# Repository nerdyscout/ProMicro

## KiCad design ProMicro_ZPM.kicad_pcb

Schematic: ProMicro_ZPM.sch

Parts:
A1: Sparkfun_Pro_Micro_3V3; Sparkfun_Pro_Micro
C1: 10µF; CP_Elec_4x3
C2: 1µ; C_0603_1608Metric
C3, C4: 4.7µ; C_0603_1608Metric
J1: Screw_Terminal_01x05; TerminalBlock_TE_282834-5_1x05_P2.54mm_Horizontal
J3: JST; JST_PH_S2B-PH-SM4-TB_1x02-1MP_P2.00mm_Horizontal
JP2, JP3: SolderJumper_3_Bridged12; SolderJumper-3_P1.3mm_Bridged12_RoundedPad1.0x1.5mm
JP4: SolderJumper_2_Open; SolderJumper-2_P1.3mm_Open_RoundedPad1.0x1.5mm
L1: CDRH2D18_HPNP-100C; HPNP-100NC
LOGO1: Logo_Open_Hardware_Small; OSHW-Symbol_6.7x6mm_SilkScreen
Q1: BC847; SOT-23
R1: 2k; R_0603_1608Metric
TP1: TestPoint; TestPoint_Pad_D2.5mm
U1: LTC3588EDD-1PBF; MSOP-10-1EP_3x3mm_P0.5mm_EP1.68x1.88mm_ThermalVias
U2: MCP73831-2-OT; SOT-23-5

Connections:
+3V3: A1.21, C1.1, J1.3, L1.1, U1.6
/D0: JP2.2 (C), U1.9
/D1: JP3.2 (C), U1.8
/Vin2: C4.1, JP2.3 (B), JP3.1 (A), U1.7
GND: A1.4, A1.23, C1.2, C3.2, C4.2, J1.1, J3.1, JP2.1 (A), JP3.3 (B), Q1.2, R1.2, U1.11, U2.2
unnamed: C2.1, U1.3
unnamed: J1.4, U1.2
unnamed: J1.5, U1.1
unnamed: JP4.2 (B), Q1.1, U1.10
unnamed: L1.2, U1.5
unnamed: R1.1, U2.5
Reset: A1.22, JP4.1 (A), Q1.3
VBAT: C2.2, C3.1, J1.2, J3.2, TP1.1, U1.4, U2.3
VCC: A1.24, U2.4

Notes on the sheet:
default Vout = 3.3V

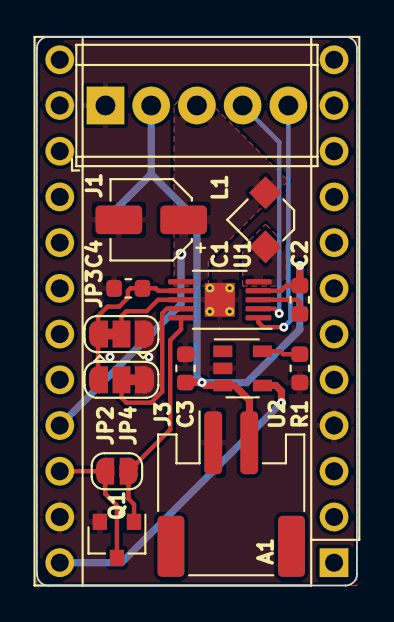
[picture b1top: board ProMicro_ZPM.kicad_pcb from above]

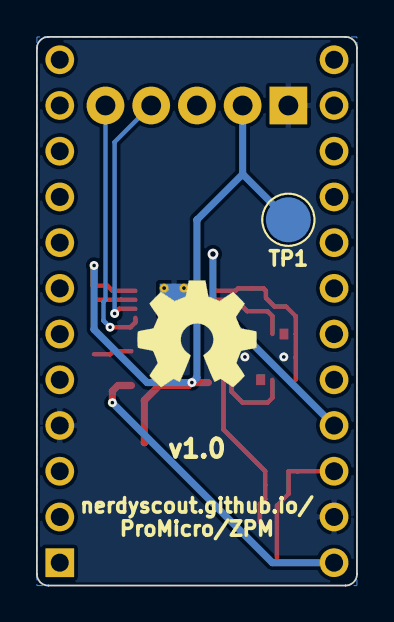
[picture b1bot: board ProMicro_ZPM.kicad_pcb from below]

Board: 2 copper layers, 17.8 x 30.5 mm, 17 parts (2 on the bottom side), 14 nets.

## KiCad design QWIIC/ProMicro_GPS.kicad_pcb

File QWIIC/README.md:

# ProMicro_QWIIC
This module can be mounted to an [Arduino Pro Mini](https://www.sparkfun.com/products/11113), [Arduino Nano](https://store.arduino.cc/arduino-nano), [Sparkfun Pro Micro](https://www.sparkfun.com/products/12587), or any other pincompatible MCU running with 3.3V.

## Documentation 
All files can be found on [Github](https://github.com/nerdyscout/ProMicro/tree/master/QWIIC).

### Schematic

### BoM
  * [interactiveHTMLBoM](https://nerdyscout.github.io/ProMicro/QWIIC/docs/bom/QWIIC-ibom.html)
  * [octopart](docs/bom/QWIIC-bom_octopart.csv)

## Hardware 
### Layout

### Gerbers
can be found within the Github [repository](gerbers).

## external
### Links
  * [hackaday.io](https://hackaday.io/project/171898-promicro)

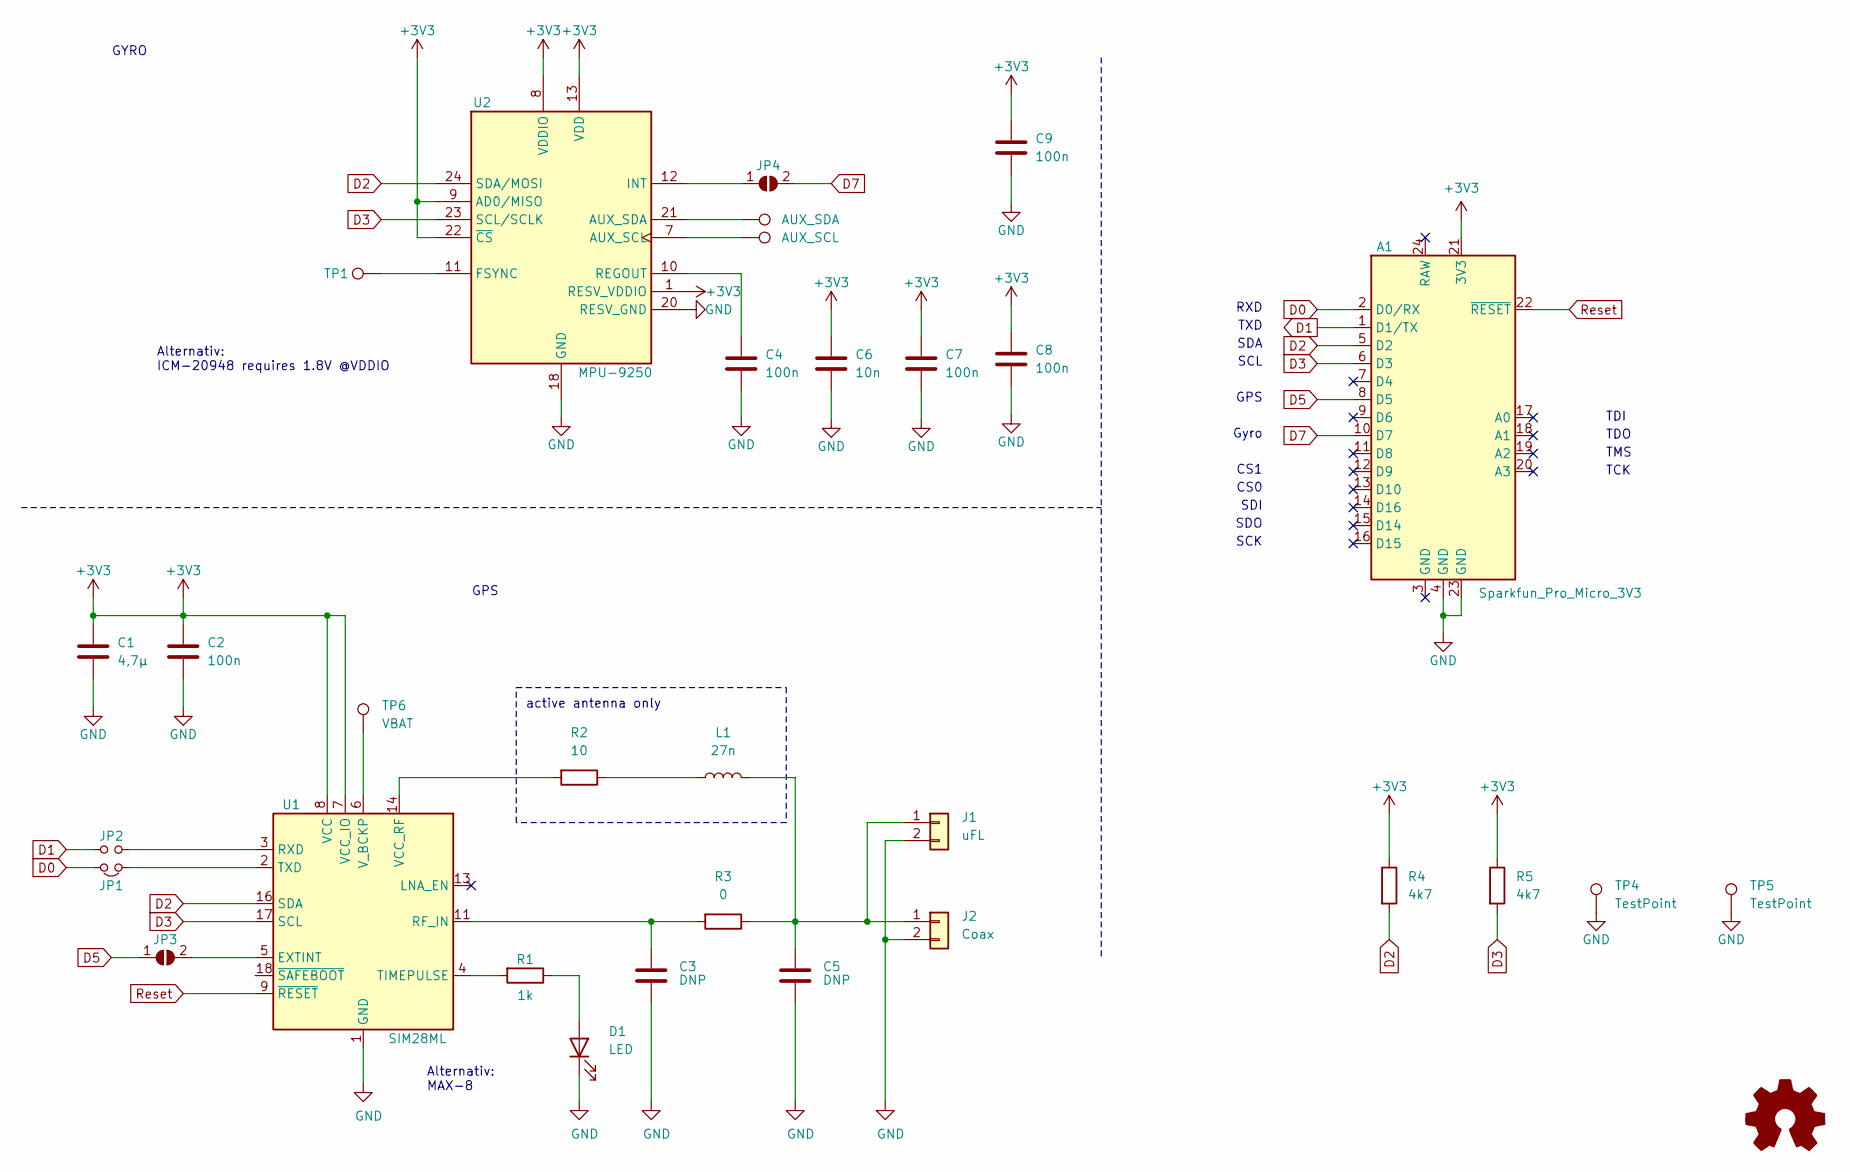
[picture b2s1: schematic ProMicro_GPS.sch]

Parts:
A1: Sparkfun_Pro_Micro_3V3; Sparkfun_Pro_Micro
C1: 4,7µ; C_0603_1608Metric; LCSC# C19666
C2, C4, C7, C8: 100n; C_0402_1005Metric; LCSC# C1525
C3, C5: DNP; C_0402_1005Metric
C6: 10n; C_0402_1005Metric; LCSC# C15195
C9: 100n; C_0402_1005Metric; LCSC# C15195
D1: LED; LED_0603_1608Metric; LCSC# C72041
J1: uFL; U.FL_Hirose_U.FL-R-SMT-1_Vertical
J2: Coax; SMA_Samtec_SMA-J-P-H-ST-EM1_EdgeMount
JP1: Jumper_NC_Small; SolderJumper-2_P1.3mm_Bridged_RoundedPad1.0x1.5mm
JP2: Jumper_NO_Small; SolderJumper-2_P1.3mm_Open_RoundedPad1.0x1.5mm
JP3, JP4: SolderJumper_2_Open; SolderJumper-2_P1.3mm_Open_RoundedPad1.0x1.5mm
L1: 27n; L_0402_1005Metric
LOGO1: Logo_Open_Hardware_Small; OSHW-Symbol_6.7x6mm_SilkScreen
R1: 1k; R_0402_1005Metric; LCSC# C11702
R2: 10; R_0402_1005Metric
R3: 0; R_0402_1005Metric; LCSC# C17168
R4, R5: 4k7; R_0402_1005Metric; LCSC# C25900
TP1: FSYNC; TestPoint_Pad_D1.5mm
TP2: AUX_SDA; TestPoint_Pad_D1.5mm
TP3: AUX_SCL; TestPoint_Pad_D1.5mm
TP4, TP5: TestPoint; TestPoint_Pad_1.5x1.5mm
TP6: VBAT; TestPoint_THTPad_D1.5mm_Drill0.7mm
U1: SIM28ML; ublox_MAX
U2: MPU-9250; InvenSense_QFN-24_3x3mm_P0.4mm; LCSC# C71459

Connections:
+3V3: A1.21 (3V3), C1.1, C2.1, C6.1, C7.1, C8.1, C9.1, R4.1, R5.1, U1.7 (VCC_IO), U1.8 (VCC), U2.1 (RESV_VDDIO), U2.8 (VDDIO), U2.9 (AD0/MISO), U2.13 (VDD), U2.22 (~CS)
D0: A1.2 (D0/RX), JP1.2
D1: A1.1 (D1/TX), JP2.2
D2: A1.5 (D2), R4.2, U1.16 (SDA), U2.24 (SDA/MOSI)
D3: A1.6 (D3), R5.2, U1.17 (SCL), U2.23 (SCL/SCLK)
D5: A1.8 (D5), JP3.1 (A)
D7: A1.10 (D7), JP4.2 (B)
GND: A1.4 (GND), A1.23 (GND), C1.2, C2.2, C3.2, C4.2, C5.2, C6.2, C7.2, C8.2, C9.2, D1.1 (K), J1.2, J2.2, TP4.1, TP5.1, U1.1 (GND), U1.10 (GND), U1.12 (GND), U2.18 (GND), U2.20 (RESV_GND)
unnamed: C3.1, R3.2, U1.11 (RF_IN)
unnamed: C4.1, U2.10 (REGOUT)
unnamed: C5.1, J1.1, J2.1, L1.2, R3.1
unnamed: D1.2 (A), R1.1
unnamed: JP1.1, U1.2 (TXD)
unnamed: JP2.1, U1.3 (RXD)
unnamed: JP3.2 (B), U1.5 (EXTINT)
unnamed: JP4.1 (A), U2.12 (INT)
unnamed: L1.1, R2.1
unnamed: R1.2, U1.4 (TIMEPULSE)
unnamed: R2.2, U1.14 (VCC_RF)
unnamed: TP1.1, U2.11 (FSYNC)
unnamed: TP2.1, U2.21 (AUX_SDA)
unnamed: TP3.1, U2.7 (AUX_SCL)
unnamed: TP6.1, U1.6 (V_BCKP)
Reset: A1.22 (~RESET), U1.9 (~RESET)

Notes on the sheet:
TDI
TDO
TMS
TCK
SCL
SDA
TXD
RXD
SCK
SDO
SDI
CS0
CS1
Gyro
GPS
GYRO
active antenna only
Alternativ: ICM-20948 requires 1.8V @VDDIO
Alternativ: MAX-8

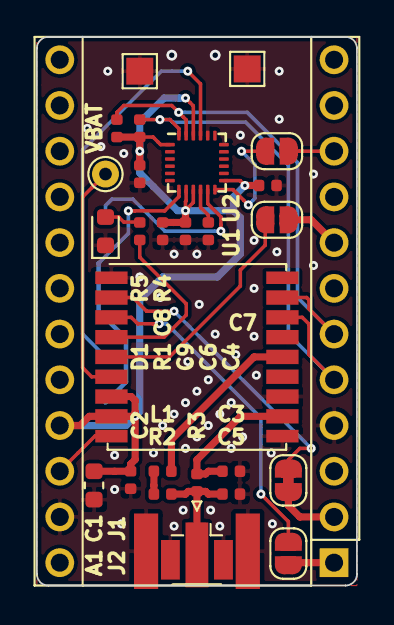
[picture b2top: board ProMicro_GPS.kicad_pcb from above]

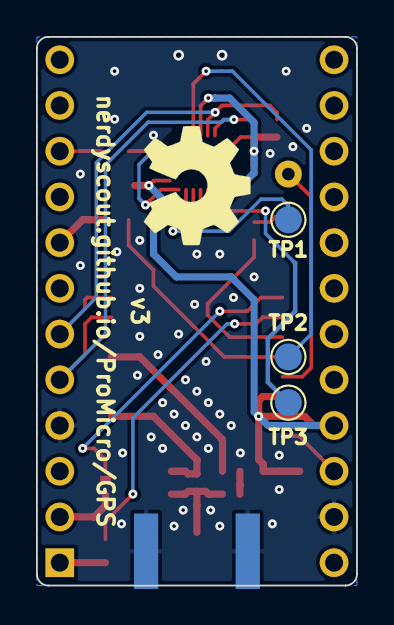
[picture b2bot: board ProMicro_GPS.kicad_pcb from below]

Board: 2 copper layers, 17.8 x 30.5 mm, 32 parts (4 on the bottom side), 24 nets.

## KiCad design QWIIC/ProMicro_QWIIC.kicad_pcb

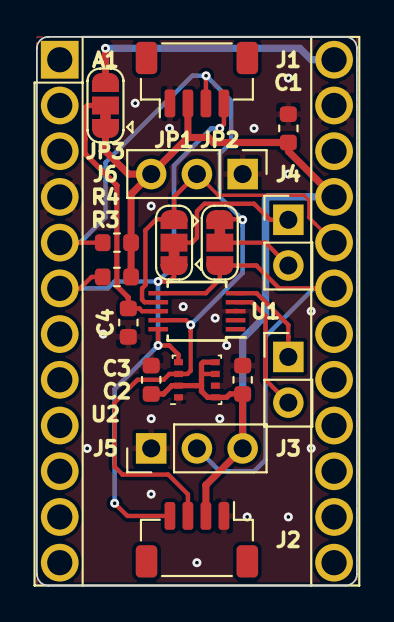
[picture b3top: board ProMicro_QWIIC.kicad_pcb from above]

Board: 2 copper layers, 17.8 x 30.5 mm, 19 parts (1 on the bottom side), 12 nets.

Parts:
A1: Sparkfun_Pro_Micro_3V3; Sparkfun_Pro_Micro
C1: 10µ; C_0603_1608Metric
C2, C3, C4: 100n; C_0603_1608Metric
J1, J2: Qwiic; JST_SH_BM04B-SRSS-TB_1x04-1MP_P1.00mm_Vertical
J3, J4: Conn_01x02; PinHeader_1x02_P2.54mm_Vertical
J5, J6: Conn_01x03; PinHeader_1x03_P2.54mm_Vertical
JP1, JP2, JP3: SolderJumper_3_Bridged12; SolderJumper-3_P1.3mm_Bridged12_RoundedPad1.0x1.5mm
LOGO1: Logo_Open_Hardware_Small; OSHW-Symbol_6.7x6mm_SilkScreen
R3, R4: 4k7; R_0603_1608Metric
U1: ADS1015IDGS; TSSOP-10_3x3mm_P0.5mm
U2: BME280; Bosch_LGA-8_2.5x2.5mm_P0.65mm_ClockwisePinNumbering

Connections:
+3V3: A1.21, C1.1, C2.1, C3.1, J1.2, J2.2, J5.3, J6.3, JP3.1, R3.2, R4.2, U2.2, U2.5, U2.6, U2.8
+5V: A1.24, JP3.3
/LIPO_VBAT: J3.2, U1.4
A2: A1.19, J5.2, JP2.3, U1.6
A3: A1.20, J6.2, JP1.3, U1.7
GND: A1.4, A1.23, C1.2, C2.2, C3.2, C4.2, J1.1, J2.1, J5.1, J6.1, U1.3, U2.1, U2.7
unnamed: C4.1, JP3.2, U1.8
unnamed: J3.1, U1.5
unnamed: J4.1, JP1.2
unnamed: J4.2, JP2.2
SCL: A1.6, J1.4, J2.4, JP1.1, R3.1, U1.10, U2.4
SDA: A1.5, J1.3, J2.3, JP2.1, R4.1, U1.9, U2.3

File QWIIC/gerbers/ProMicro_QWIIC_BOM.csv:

Component;Description;Part;References;Value;Footprint;Quantity Per PCB;Datasheet;manf#;lcsc#
1;Unpolarized capacitor;C;C2 C3 C4;100n;C_0603_1608Metric;3;~;;
2;Unpolarized capacitor;C;C1;10µ;C_0603_1608Metric;1;~;;
3;Generic connector, single row, 01x02, script generated (kicad-library-utils/schlib/autogen/connector/);Conn_01x02;J3 J4;Conn_01x02;PinHeader_1x02_P2.54mm_Vertical;2;~;;
4;Generic connector, single row, 01x03, script generated (kicad-library-utils/schlib/autogen/connector/);Conn_01x03;J5 J6;Conn_01x03;PinHeader_1x03_P2.54mm_Vertical;2;~;;
5;Generic connector, single row, 01x04, script generated (kicad-library-utils/schlib/autogen/connector/);Conn_01x04;J1 J2;Qwiic;JST_SH_BM04B-SRSS-TB_1x04-1MP_P1.00mm_Vertical;2;~;;
6;Resistor;R;R3 R4;4k7;R_0603_1608Metric;2;~;RC0402FR-074K7L;C105871
7;Ultra-Small, Low-Power, I2C-Compatible, 3.3-kSPS, 12-Bit ADCs With Internal Reference, Oscillator, and Programmable Comparator, VSSOP-10;ADS1015IDGS;U1;ADS1015IDGS;TSSOP-10_3x3mm_P0.5mm;1;http://www.ti.com/lit/ds/symlink/ads1015.pdf;;
8;3-in-1 sensor, humidity, pressure, temperature, I2C and SPI interface, 1.71-3.6V, LGA-8;BME280;U2;BME280;Bosch_LGA-8_2.5x2.5mm_P0.65mm_ClockwisePinNumbering;1;https://ae-bst.resource.bosch.com/media/_tech/media/datashee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;;

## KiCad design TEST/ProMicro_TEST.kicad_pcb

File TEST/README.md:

# ProMicro_TEST
This module can be mounted to an [Arduino Pro Mini](https://www.sparkfun.com/products/11113), [Arduino Nano](https://store.arduino.cc/arduino-nano), [Sparkfun Pro Micro](https://www.sparkfun.com/products/12587), or any other pincompatible MCU running with 3.3V.

## Documentation
All files can be found on [Github](https://github.com/nerdyscout/ProMicro/tree/master/TEST).

### Schematic

### Layout

### BoM
  * [interactiveHTMLBoM](https://nerdyscout.github.io/ProMicro/TEST/docs/bom/ProMicro_TEST-ibom.html)
  * [octopart.csv](docs/bom/ProMicro_TEST-bom_octopart.csv)
  * [jlcpcb.csv](gerbers/ProMicro_TEST-bom_jlcpcb.csv)

## Gerbers
can be found within the Github [repository](gerbers).

## Code
| | TEST1 | TEST2 |
| --- | --- | --- |
| Arduino Nano | tbd | [TEST](examples/Arduino_Nano_TEST/Arduino_Nano_TEST.ino) |
| Sparkfun ProMicro | [TEST](examples/Sparkfun_ProMicro_TEST/Sparkfun_ProMicro_TEST.ino) | [TEST](examples/Sparkfun_ProMicro_TEST/Sparkfun_ProMicro_TEST.ino) |

## Links
  * [hackaday.io](https://hackaday.io/project/171898-promicro)

## License
Copyright Stefan Herold 2020

This documentation describes Open Hardware and is licensed under the CERN OHL v.1.2.

You may redistribute and modify this documentation under the terms of the CERN OHL v.1.2. (http://ohwr.org/cernohl). This documentation is distributed WITHOUT ANY EXPRESS OR IMPLIED WARRANTY, INCLUDING OF MERCHANTABILITY, SATISFACTORY QUALITY AND FITNESS FOR A PARTICULAR PURPOSE. Please see the CERN OHL v.1.2 for applicable conditions

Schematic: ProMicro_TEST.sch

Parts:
A1: Sparkfun_Pro_Micro
C1: 100n; C_0402_1005Metric
C4: 10µ; C_0603_1608Metric
LOGO1: Logo_Open_Hardware_Small; OSHW-Symbol_6.7x6mm_SilkScreen
R3: 4k7; R_0402_1005Metric; MPN RC0402FR-074K7L
R4: 4k7; R_0402_1005Metric; MPN RC0402FR-074K7L; lcsc# C105871

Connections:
+3V3: A1.21, C1.1, C4.1, R3.2, R4.2
GND: A1.3, A1.4, A1.23, C1.2, C4.2
SCL: A1.6, R3.1
SDA: A1.5, R4.1

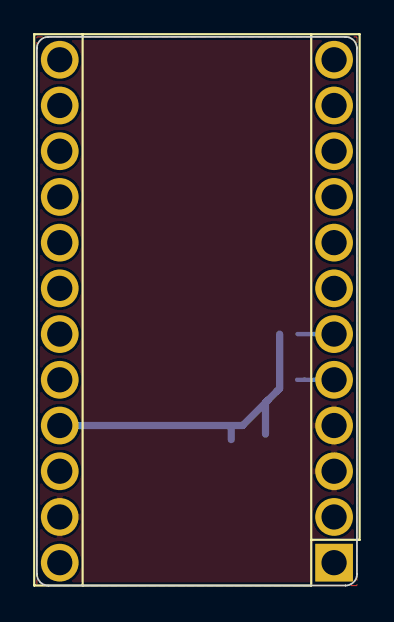
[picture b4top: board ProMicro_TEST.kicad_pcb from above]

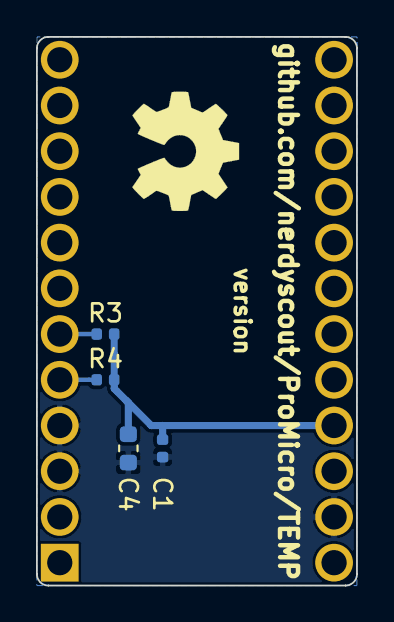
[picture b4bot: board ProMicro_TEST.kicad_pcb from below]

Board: 2 copper layers, 17.8 x 30.5 mm, 6 parts (5 on the bottom side), 4 nets.

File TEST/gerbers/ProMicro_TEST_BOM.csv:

Component;Description;Part;References;Value;Footprint;Quantity Per PCB;Datasheet;manf#;lcsc#
1;Unpolarized capacitor;C;C1;100n;C_0402_1005Metric;1;~;;
2;Unpolarized capacitor;C;C4;10µ;C_0603_1608Metric;1;~;;
3;Resistor;R;R3 R4;4k7;R_0402_1005Metric;2;~;RC0402FR-074K7L;C105871

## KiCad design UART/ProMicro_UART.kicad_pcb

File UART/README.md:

# ProMicro_UART 
USB to Serial, SPI, I2C or JTAG

## Documentation 
All files can be found on [Github](https://github.com/nerdyscout/ProMicro/tree/master/UART).

### Schematic

### BoM
  * [interactiveHTMLBoM](https://nerdyscout.github.io/ProMicro/UART/docs/bom/UART-ibom.html)
  * [octopart](docs/bom/UART-bom_octopart.csv)

## Hardware 
### Layout

### Gerbers
can be found within the Github [repository](gerbers).

## external
### Links
  * [hackaday.io](https://hackaday.io/project/171898-promicro)

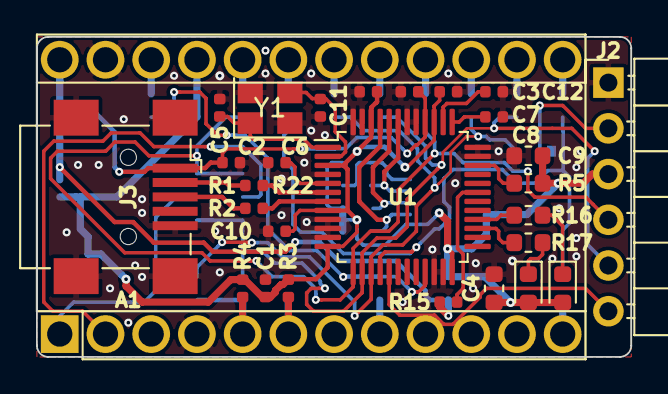
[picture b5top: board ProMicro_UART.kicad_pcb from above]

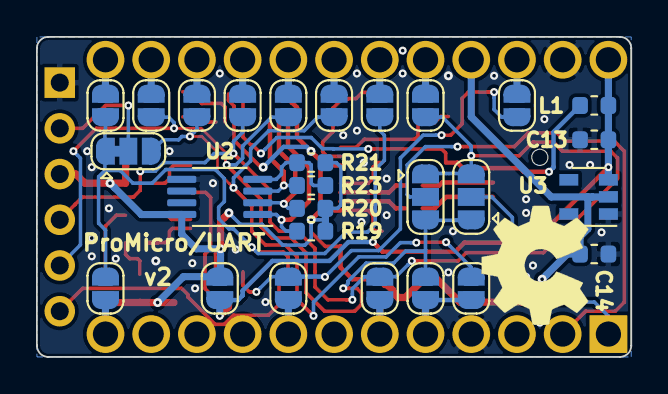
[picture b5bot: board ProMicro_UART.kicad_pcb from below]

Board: 2 copper layers, 33.0 x 17.8 mm, 56 parts (28 on the bottom side), 43 nets.

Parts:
A1: Sparkfun_Pro_Micro_3V3; Sparkfun_Pro_Micro
C1, C3, C7, C8, C10, C11, C12: 100n; C_0402_1005Metric
C2: 4.7µ; C_0402_1005Metric
C4: 10µ; C_0603_1608Metric
C5, C6: 27p; C_0402_1005Metric
C9: 4.7µ; R_0603_1608Metric
C13, C14: 1µ; C_0603_1608Metric
D1: TX; LED_0603_1608Metric
D2: RX; LED_0603_1608Metric
J2: Conn_01x06; PinHeader_1x06_P2.54mm_Horizontal
J3: USB_B_Mini; USB_Mini-B_Wuerth_65100516121_Horizontal
JP1, JP2, JP3, JP4, JP5, JP6, JP7, JP8, JP9, JP12, JP13, JP14, JP15, JP17, JP18: Jumper_NO_Small; SolderJumper-2_P1.3mm_Open_RoundedPad1.0x1.5mm
JP10, JP11: Jumper_3_Bridged12; SolderJumper-3_P1.3mm_Open_RoundedPad1.0x1.5mm
JP16: Jumper_3_Bridged12; SolderJumper-3_P1.3mm_Bridged12_RoundedPad1.0x1.5mm
L1: 0; L_0603_1608Metric
LOGO1: Logo_Open_Hardware_Small; OSHW-Symbol_6.7x6mm_SilkScreen
R1, R2: 22; R_0402_1005Metric
R3, R4: 4k7; R_0402_1005Metric
R5: 1k; R_0603_1608Metric
R15: 39k; R_0402_1005Metric
R16, R17: 220; R_0603_1608Metric
R19, R20, R21: 10k; R_0603_1608Metric
R22: 12k; R_0402_1005Metric
R23: 2k; R_0603_1608Metric
U1: FT232H; LQFP-48_7x7mm_P0.5mm
U2: 93CxxB; MSOP-8_3x3mm_P0.65mm
U3: AZ1117-3.3; SOT-23-5
Y1: 12MHz; Crystal_SMD_3225-4Pin_3.2x2.5mm

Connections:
+3V3: A1.21, C1.1, C4.1, C9.1, C10.2, C11.2, C12.1, C14.1, D1.2, D2.2, J2.3, JP18.2, R3.2, R4.2, R5.2, R19.2, R20.2, R21.2, U1.3, U1.8, U1.12, U1.24, U1.39, U1.46, U2.8, U3.2
+5V: C13.1, JP18.1, L1.1, R15.2, U3.3
/CIPO: A1.15, JP3.2
/COPI: A1.14, JP2.2
/CS0: A1.13, JP5.2
/CS1: A1.12, JP4.2
/EECLK: R20.1, U1.44, U2.2
/EECS: R19.1, U1.45, U2.1
/EEDAT: R23.1, U1.43, U2.3
/PWM: A1.8, JP12.2
/RXD: A1.1, JP10.2
/SCK: A1.16, JP1.2
/SCL: A1.6, JP15.2, R3.1
/SDA: A1.5, JP13.2, JP14.2, R4.1
/TCK: A1.20, JP6.2
/TDI: A1.17, JP7.2
/TDO: A1.18, JP8.2
/TMS: A1.19, JP9.2
/TXD: A1.2, JP11.2
/~RST: A1.22, JP17.2
ACBUS0: JP12.1, JP17.1, U1.21
ADBUS0: J2.4, JP1.1, JP6.1, JP10.3, JP11.1, JP15.1, U1.13
ADBUS1: J2.5, JP2.1, JP7.1, JP10.1, JP11.3, JP13.1, U1.14
ADBUS2: JP3.1, JP8.1, JP14.1, JP16.3, U1.15
ADBUS3: JP4.1, JP5.1, JP9.1, JP16.1, U1.16
ADBUS4: J2.6, U1.17
GND: A1.4, A1.23, C1.2, C2.2, C3.2, C4.2, C5.2, C6.2, C7.2, C8.2, C9.2, C10.1, C11.1, C12.2, C13.2, C14.2, J2.1, J3.5, J3.6, R22.2, U1.4, U1.9, U1.10, U1.11, U1.22, U1.23, U1.35, U1.36, U1.41, U1.42, U1.47, U1.48, U2.5, U3.1, Y1.2, Y1.4
unnamed: C2.1, C3.1, J3.1, L1.2, U1.40
unnamed: C5.1, U1.1, Y1.1
unnamed: C6.1, U1.2, Y1.3
unnamed: C7.1, U1.38
unnamed: C8.1, U1.37
unnamed: D1.1, R16.2
unnamed: D2.1, R17.2
unnamed: J2.2, JP16.2
unnamed: R1.1, U1.6
unnamed: R2.1, U1.7
unnamed: R5.1, U1.34
unnamed: R21.1, R23.2, U2.4
unnamed: R22.1, U1.5
PWRSAV: R15.1, U1.31
RXLED: R17.1, U1.27
TXLED: R16.1, U1.28

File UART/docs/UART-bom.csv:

References;Description;Part;Value;Qty;lcsc#;mpn
A1;;Sparkfun_Pro_Micro;Sparkfun_Pro_Micro_3V3;1;;
C5 C6;Unpolarized capacitor;C;27p;2;C19702;0402CG270J500NTN
C1 C3 C7 C8 C10 C11 C12;Unpolarized capacitor;C;100n;7;C1525;CL05B104KO5NNNC
C13 C14;Unpolarized capacitor;C;1µ;2;C15849;CL10A105KB8NNNC
C2;Unpolarized capacitor;C;4.7µ;1;C23733;CL05A475MP5NRNC
C9;Unpolarized capacitor;C;4.7µ;1;C19666;CL10A475KO8NNNC
C4;Unpolarized capacitor;C;10µ;1;C15525;CL10A106KP8NNNC
D2;Light emitting diode;LED;RX;1;C72043;19-217/GHC-YR1S2/3T
D1;Light emitting diode;LED;TX;1;C72043;19-217/GHC-YR1S2/3T
J2;Generic connector, single row, 01x06, script generated (kicad-library-utils/schlib/autogen/connector/);Conn_01x06;Conn_01x06;1;;
J1;USB Mini Type B connector;USB_B_Mini;USB_B_Mini;1;;
L1;Inductor, small symbol;L_Small;0;1;;
R1 R2;Resistor;R;22;2;C25092;0402WGF220JTCE
R16 R17;Resistor;R;220;2;C22962;0603WAF2200T5E
R5;Resistor;R;1k;1;C21190;0603WAF1001T5E
R23;Resistor;R;2k;1;C22975;0603WAF2001T5E
R3 R4;Resistor;R;4k7;2;C25900;0402WGF4701TCE
R19 R20 R21;Resistor;R;10k;3;C25804;0603WAF1002T5E
R22;Resistor;R;12k;1;C25752;0402WGF1202TCE
R15;Resistor;R;39k;1;C25783;0402WGF3902TCE
U2;Serial EEPROM, 93 Series, 5.0V, DIP-8/SOIC-8;93CxxB;93CxxB;1;;
U3;1A 20V Fixed LDO Linear Regulator, 3.3V, SOT-89/SOT-223/TO-220/TO-252/TO-263;AZ1117-3.3;AZ1117-3.3;1;;
U1;Hi Speed Single Channel USB UART/FIFO, LQFP/QFN-48;FT232H;FT232H;1;C51997;FT232HL
Y1;Four pin crystal, GND on pins 2 and 4, small symbol;Crystal_GND24_Small;12MHz;1;;

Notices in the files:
QWIIC/README.md:
Documentation [![CC BY-SA](../img/ccbysa.png)](docs/LICENSE.TXT):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
ProMicro_GPS.sch:
CERN Open Hardware Licence v1.2
